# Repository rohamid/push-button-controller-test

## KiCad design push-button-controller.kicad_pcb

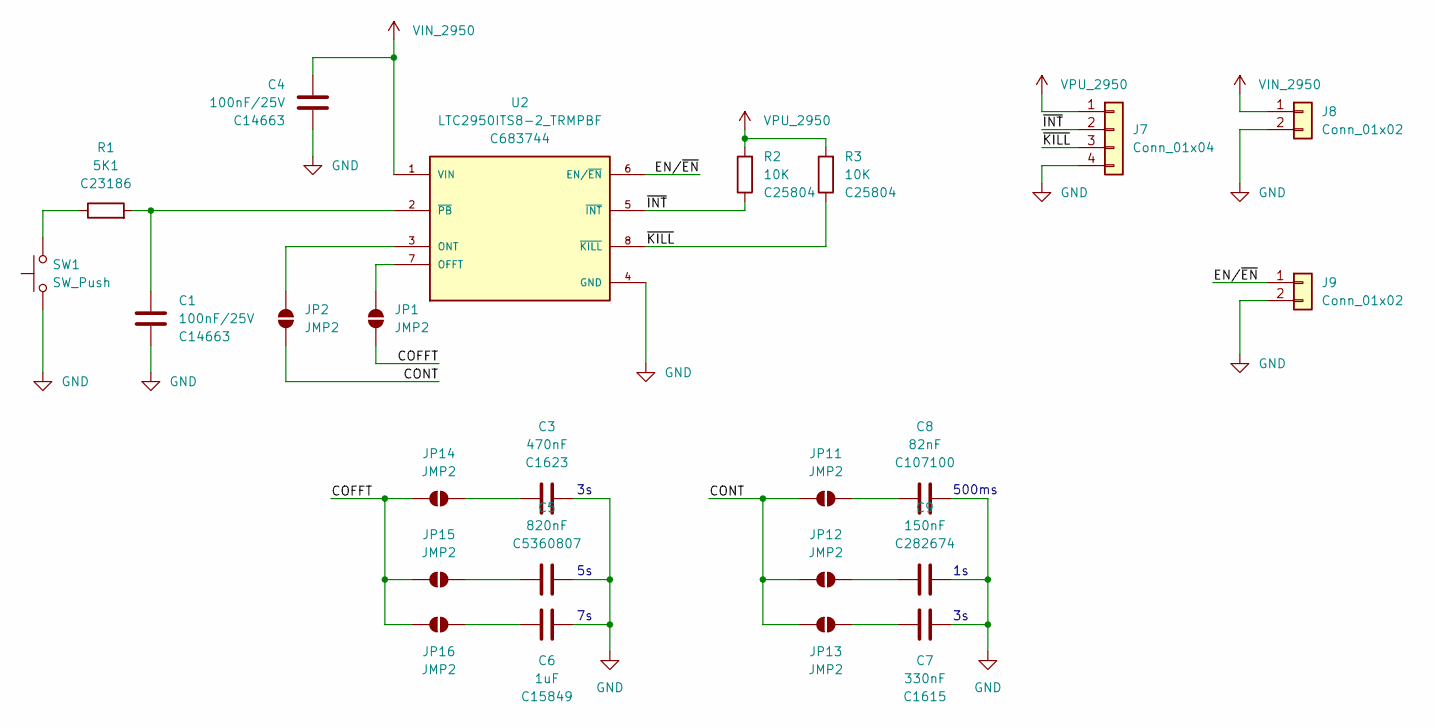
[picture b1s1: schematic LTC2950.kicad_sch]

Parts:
C1, C4: 100nF/25V; C_0603_1608Metric; JLCPCB Part # C14663
C3: 470nF; C_0603_1608Metric; JLCPCB Part # C1623
C5: 820nF; C_0603_1608Metric; JLCPCB Part # C5360807
C6: 1uF; C_0603_1608Metric; JLCPCB Part # C15849
C7: 330nF; C_0603_1608Metric; JLCPCB Part # C1615
C8: 82nF; C_0603_1608Metric; JLCPCB Part # C107100
C9: 150nF; C_0603_1608Metric; JLCPCB Part # C282674
J7: Conn_01x04; PinHeader_1x04_P2.54mm_Vertical
J8, J9: Conn_01x02; PinHeader_1x02_P2.54mm_Vertical
JP1, JP2, JP11, JP12, JP13, JP14, JP15, JP16: JMP2; SolderJumper-2_P1.3mm_Open_RoundedPad1.0x1.5mm
R1: 5K1; R_0603_1608Metric; JLCPCB Part # C23186
R2, R3: 10K; R_0603_1608Metric; JLCPCB Part # C25804
SW1: SW_Push; SW_PUSH_6mm
U2: LTC2950ITS8-2_TRMPBF; LTC2950ITS8-2; PARTREV D; JLCPCB Part # C683744

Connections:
/LTC2950/COFFT: JP1.1 (A), JP14.2 (B), JP15.2 (B), JP16.2 (B)
/LTC2950/CONT: JP2.1 (A), JP11.2 (B), JP12.2 (B), JP13.2 (B)
/LTC2950/EN/~EN: J9.1, U2.6 (EN/~EN)
/LTC2950/~INT: J7.2, R2.1, U2.5 (~INT)
/LTC2950/~KILL: J7.3, R3.1, U2.8 (~KILL)
GND: C1.2, C3.2, C4.2, C5.2, C6.2, C7.2, C8.2, C9.2, J7.4, J8.2, J9.2, SW1.1, U2.4 (GND); also elsewhere on the board
unnamed: JP1.2 (B), U2.7 (OFFT)
unnamed: JP2.2 (B), U2.3 (ONT)
unnamed: C8.1, JP11.1 (A)
unnamed: C9.1, JP12.1 (A)
unnamed: C7.1, JP13.1 (A)
unnamed: C3.1, JP14.1 (A)
unnamed: C5.1, JP15.1 (A)
unnamed: C6.1, JP16.1 (A)
unnamed: R1.1, SW1.2
unnamed: C1.1, R1.2, U2.2 (~PB)
VIN_2950: C4.1, J8.1, U2.1 (VIN)
VPU_2950: J7.1, R2.2, R3.2

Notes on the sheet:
500ms

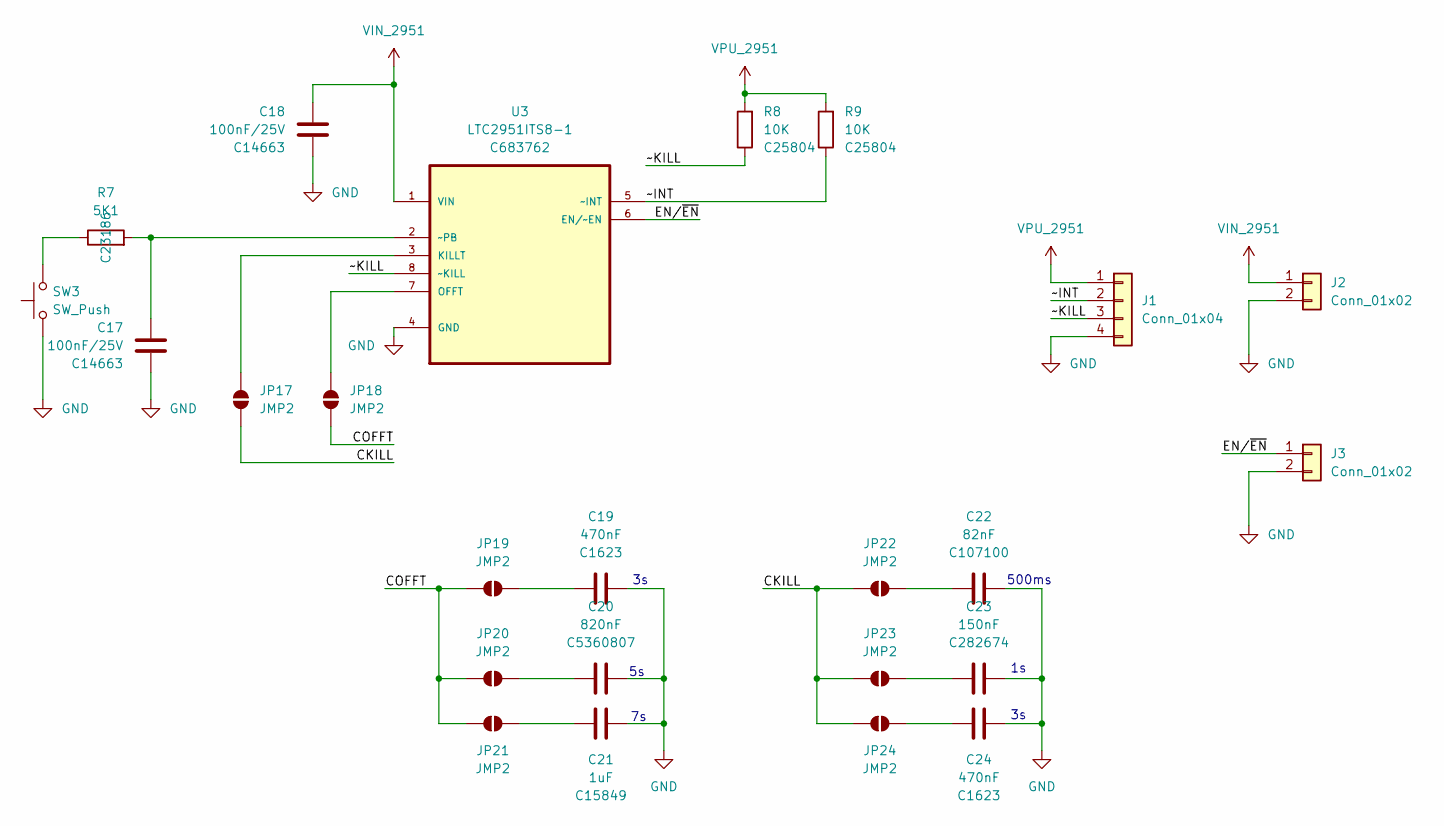
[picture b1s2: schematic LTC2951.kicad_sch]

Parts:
C17, C18: 100nF/25V; C_0603_1608Metric; JLCPCB Part # C14663
C19, C24: 470nF; C_0603_1608Metric; JLCPCB Part # C1623
C20: 820nF; C_0603_1608Metric; JLCPCB Part # C5360807
C21: 1uF; C_0603_1608Metric; JLCPCB Part # C15849
C22: 82nF; C_0603_1608Metric; JLCPCB Part # C107100
C23: 150nF; C_0603_1608Metric; JLCPCB Part # C282674
J1: Conn_01x04; PinHeader_1x04_P2.54mm_Vertical
J2, J3: Conn_01x02; PinHeader_1x02_P2.54mm_Vertical
JP17, JP18, JP19, JP20, JP21, JP22, JP23, JP24: JMP2; SolderJumper-2_P1.3mm_Open_RoundedPad1.0x1.5mm
R7: 5K1; R_0603_1608Metric; JLCPCB Part # C23186
R8, R9: 10K; R_0603_1608Metric; JLCPCB Part # C25804
SW3: SW_Push; SW_PUSH_6mm
U3: LTC2951ITS8-1; MPN LTC2951ITS8-1#TRMPBF; JLCPCB Part # C683762

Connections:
/LTC2951/CKILL: JP17.1 (A), JP22.2 (B), JP23.2 (B), JP24.2 (B)
/LTC2951/COFFT: JP18.1 (A), JP19.2 (B), JP20.2 (B), JP21.2 (B)
/LTC2951/EN/~EN: J3.1, U3.6 (EN/~EN)
/LTC2951/~INT: J1.2, R9.1, U3.5 (~INT)
/LTC2951/~KILL: J1.3, R8.1, U3.8 (~KILL)
GND: C17.2, C18.2, C19.2, C20.2, C21.2, C22.2, C23.2, C24.2, J1.4, J2.2, J3.2, SW3.1, U3.4 (GND); also elsewhere on the board
unnamed: JP17.2 (B), U3.3 (KILLT)
unnamed: JP18.2 (B), U3.7 (OFFT)
unnamed: C19.1, JP19.1 (A)
unnamed: C20.1, JP20.1 (A)
unnamed: C21.1, JP21.1 (A)
unnamed: C22.1, JP22.1 (A)
unnamed: C23.1, JP23.1 (A)
unnamed: C24.1, JP24.1 (A)
unnamed: R7.1, SW3.2
unnamed: C17.1, R7.2, U3.2 (~PB)
VIN_2951: C18.1, J2.1, U3.1 (VIN)
VPU_2951: J1.1, R8.2, R9.2

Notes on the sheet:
500ms

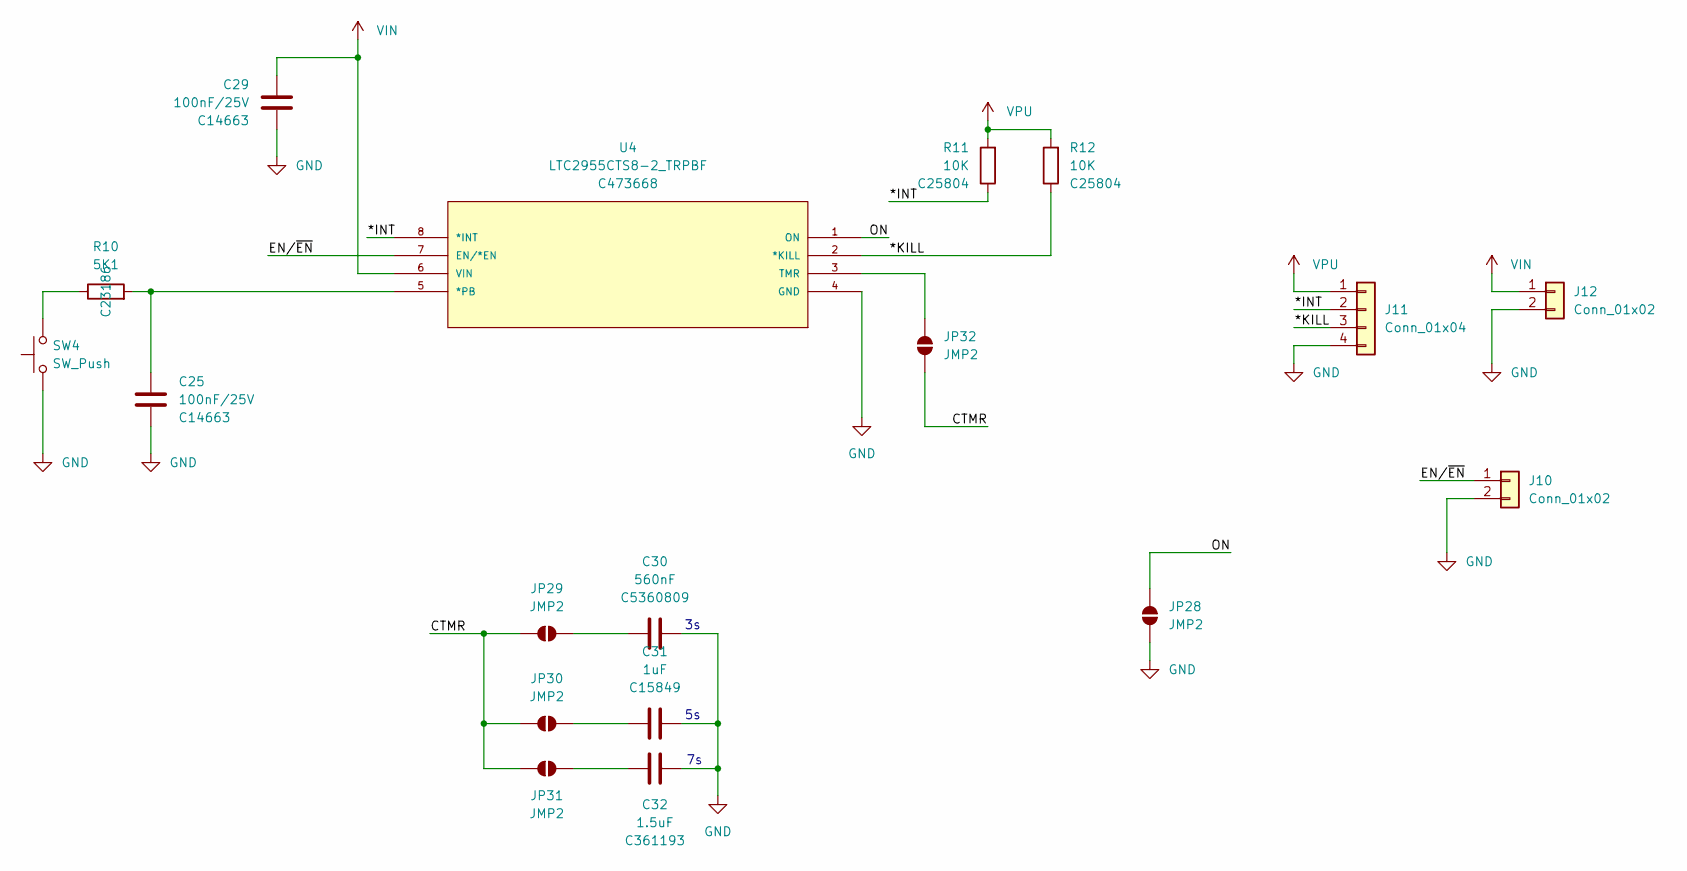
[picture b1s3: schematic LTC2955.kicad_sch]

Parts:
C25, C29: 100nF/25V; C_0603_1608Metric; JLCPCB Part # C14663
C30: 560nF; C_0603_1608Metric; JLCPCB Part # C5360809
C31: 1uF; C_0603_1608Metric; JLCPCB Part # C15849
C32: 1.5uF; C_0603_1608Metric; JLCPCB Part # C361193
J10, J12: Conn_01x02; PinHeader_1x02_P2.54mm_Vertical
J11: Conn_01x04; PinHeader_1x04_P2.54mm_Vertical
JP28, JP29, JP30, JP31, JP32: JMP2; SolderJumper-2_P1.3mm_Open_RoundedPad1.0x1.5mm
R10: 5K1; R_0603_1608Metric; JLCPCB Part # C23186
R11, R12: 10K; R_0603_1608Metric; JLCPCB Part # C25804
SW4: SW_Push; SW_PUSH_6mm
U4: LTC2955CTS8-2_TRPBF; LTC2955CTS8-2_; MANUFACTURER_PART_NUMBER ltc2955cts82#pbf; JLCPCB Part # C473668

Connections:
/LTC2955/*INT: J11.2, R11.1, U4.8 (*INT)
/LTC2955/*KILL: J11.3, R12.1, U4.2 (*KILL)
/LTC2955/CTMR: JP29.2 (B), JP30.2 (B), JP31.2 (B), JP32.1 (A)
/LTC2955/EN/~EN: J10.1, U4.7 (EN/*EN)
/LTC2955/ON: JP28.2 (B), U4.1 (ON)
GND: C25.2, C29.2, C30.2, C31.2, C32.2, J10.2, J11.4, J12.2, JP28.1 (A), SW4.1, U4.4 (GND); also elsewhere on the board
unnamed: C30.1, JP29.1 (A)
unnamed: C31.1, JP30.1 (A)
unnamed: C32.1, JP31.1 (A)
unnamed: JP32.2 (B), U4.3 (TMR)
unnamed: R10.1, SW4.2
unnamed: C25.1, R10.2, U4.5 (*PB)
VIN: C29.1, J12.1, U4.6 (VIN)
VPU: J11.1, R11.2, R12.2

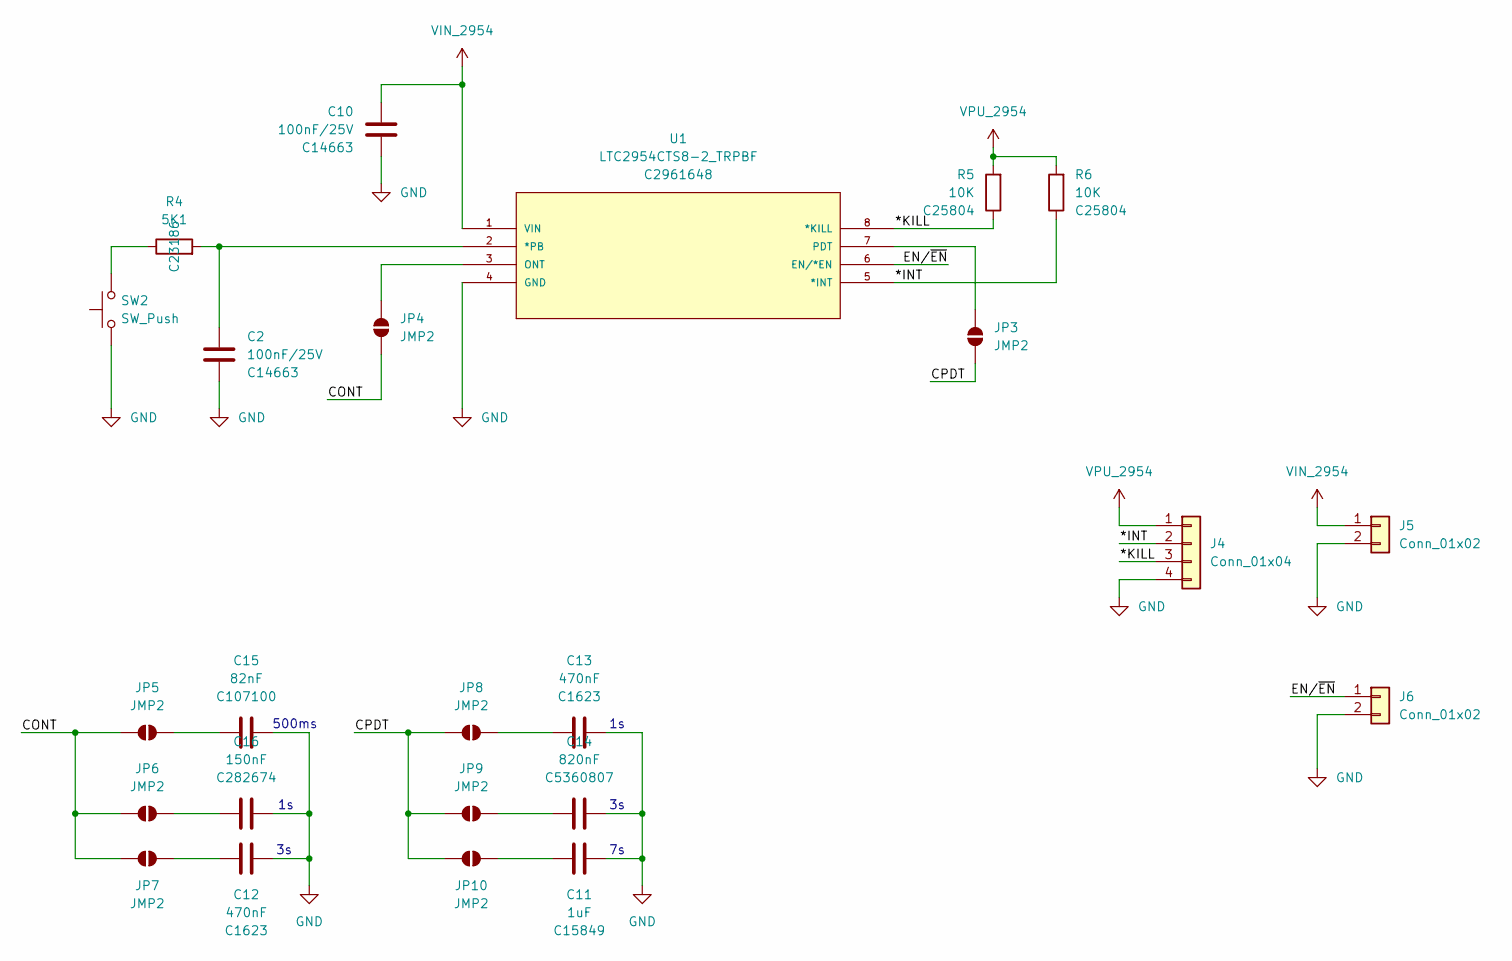
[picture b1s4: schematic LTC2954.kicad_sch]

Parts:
C2, C10: 100nF/25V; C_0603_1608Metric; JLCPCB Part # C14663
C11: 1uF; C_0603_1608Metric; JLCPCB Part # C15849
C12, C13: 470nF; C_0603_1608Metric; JLCPCB Part # C1623
C14: 820nF; C_0603_1608Metric; JLCPCB Part # C5360807
C15: 82nF; C_0603_1608Metric; JLCPCB Part # C107100
C16: 150nF; C_0603_1608Metric; JLCPCB Part # C282674
J4: Conn_01x04; PinHeader_1x04_P2.54mm_Vertical
J5, J6: Conn_01x02; PinHeader_1x02_P2.54mm_Vertical
JP3, JP4, JP5, JP6, JP7, JP8, JP9, JP10: JMP2; SolderJumper-2_P1.3mm_Open_RoundedPad1.0x1.5mm
R4: 5K1; R_0603_1608Metric; JLCPCB Part # C23186
R5, R6: 10K; R_0603_1608Metric; JLCPCB Part # C25804
SW2: SW_Push; SW_PUSH_6mm
U1: LTC2954CTS8-2_TRPBF; LTC2954CTS8-2; MANUFACTURER_PART_NUMBER ltc2954cts82; JLCPCB Part # C2961648

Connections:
/LTC2954/*INT: J4.2, R6.1, U1.5 (*INT)
/LTC2954/*KILL: J4.3, R5.1, U1.8 (*KILL)
/LTC2954/CONT: JP4.1 (A), JP5.2 (B), JP6.2 (B), JP7.2 (B)
/LTC2954/CPDT: JP3.1 (A), JP8.2 (B), JP9.2 (B), JP10.2 (B)
/LTC2954/EN/~EN: J6.1, U1.6 (EN/*EN)
GND: C2.2, C10.2, C11.2, C12.2, C13.2, C14.2, C15.2, C16.2, J4.4, J5.2, J6.2, SW2.1, U1.4 (GND); also elsewhere on the board
unnamed: JP3.2 (B), U1.7 (PDT)
unnamed: JP4.2 (B), U1.3 (ONT)
unnamed: C15.1, JP5.1 (A)
unnamed: C16.1, JP6.1 (A)
unnamed: C12.1, JP7.1 (A)
unnamed: C13.1, JP8.1 (A)
unnamed: C14.1, JP9.1 (A)
unnamed: C11.1, JP10.1 (A)
unnamed: R4.1, SW2.2
unnamed: C2.1, R4.2, U1.2 (*PB)
VIN_2954: C10.1, J5.1, U1.1 (VIN)
VPU_2954: J4.1, R5.2, R6.2

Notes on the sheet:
500ms

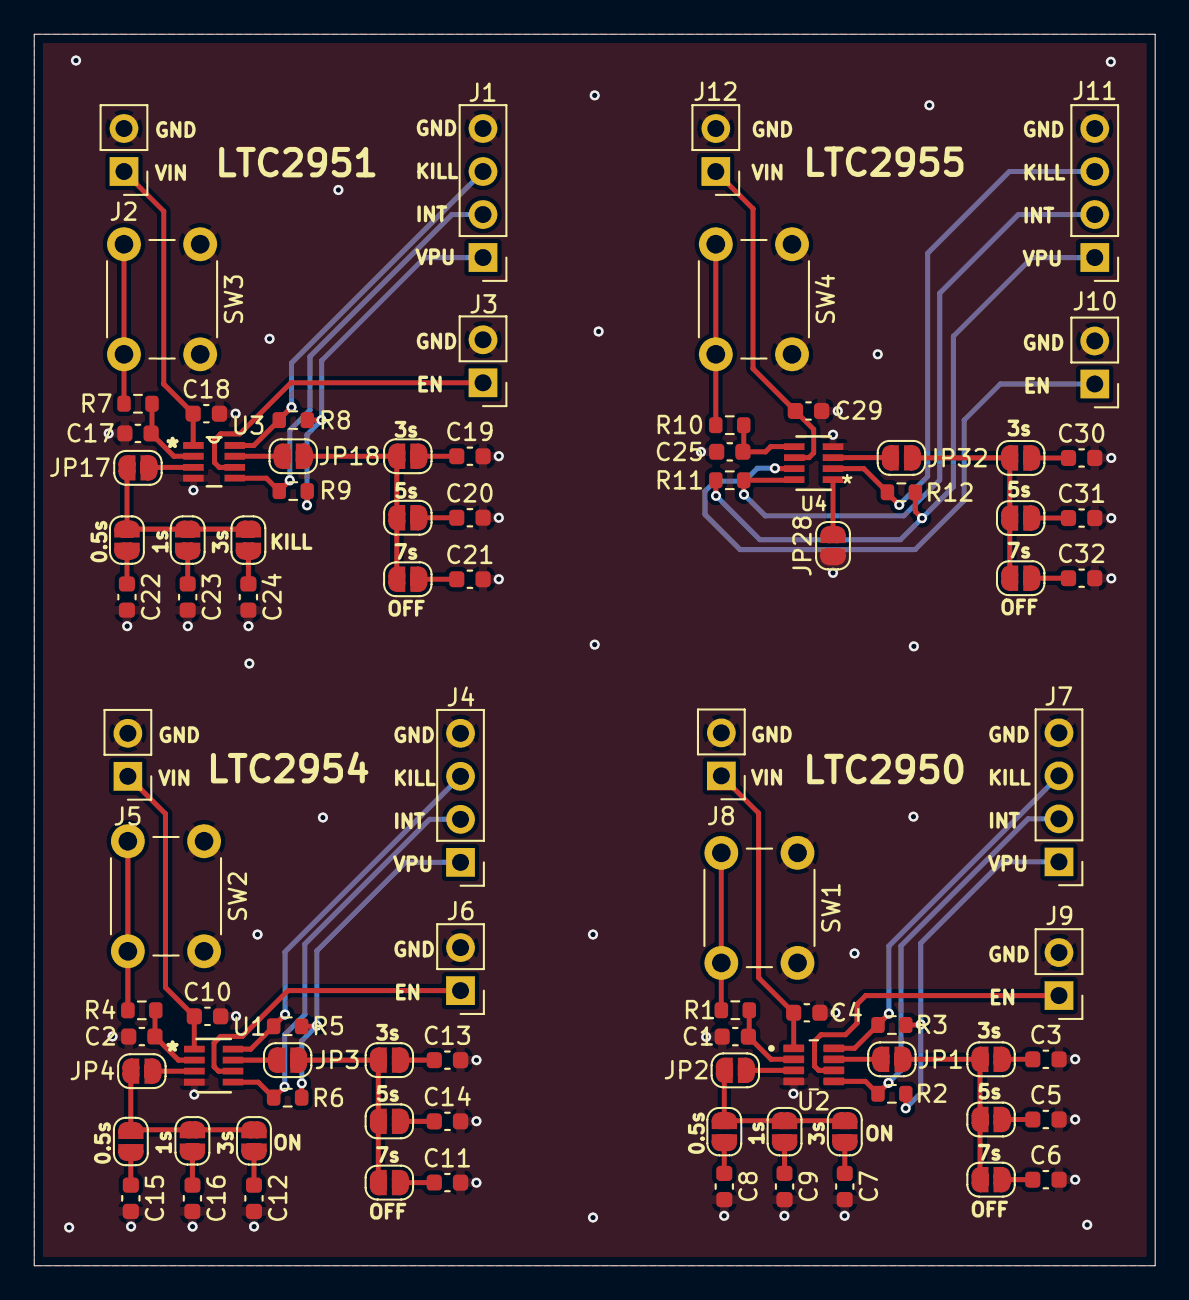
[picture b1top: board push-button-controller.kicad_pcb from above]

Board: 2 copper layers, 66.2 x 72.7 mm, 90 parts (0 on the bottom side), 65 nets.

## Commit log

2025-04-24 Added B.O.M, TODO: do PCB track layout
2025-05-02 Finished, 1st PCB order to JLCPCB
